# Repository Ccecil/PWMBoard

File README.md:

This board is to be used to expand the PWM header from a V2 Smoothieboard (or Gadgeteer) header.  

- 4 mosfet buffered PWM outputs with jumper options to select between Pullup voltages and/or disable the pullup resistor for Opendrain outputs.
- 2 Switch inputs which are debounced with passives and have optional pullup resistor/voltage.
- 1 Comparator probe input which increases the repeatability of probes and allows use of probe voltages from 3-45v (through jumper configs)
- Optional voltage input for using higher voltages on the PWM output pin3 (i.e. Running higher voltages to the servo motor or using different 5v source)

Comparator probe input jumper options

- J5 pin 3 input voltage set to
- 2.9v-5v (default)
- 5-24v (JP5-2 cut)
- 6-45v (JP5-2 and JP5-3 cut)

PWM output and Switch input jumpers.

- JP2: J6-J9 pin 3 optional voltage source select (J1 Pin 2 default, cut to use J2 Pin 1)
- JP3-1: J3 pin 1 and pin 3 pullup Voltage select
- JP3-2: J3 pin 3 pullup disable
- JP4-1: J4 pin 1 and pin 3 pullup Voltage select
- JP4-2: J4 pin 3 pullup disable
- JP5-1: J5 pin 1 Voltage select
- JP5-2: J5 pin 3 pullup cut (required for HV operation)
- JP5-3: J5 pin 3 Low/High voltage select (default low)
- JP6: J6 pin 1 pullup Voltage select
- JP7: J7 pin 1 pullup Voltage select
- JP8: J8 pin 1 pullup Voltage select
- JP9: J9 pin 1 pullup Voltage select

Jumper and connector numbers match their respective driving pin from the J1 header

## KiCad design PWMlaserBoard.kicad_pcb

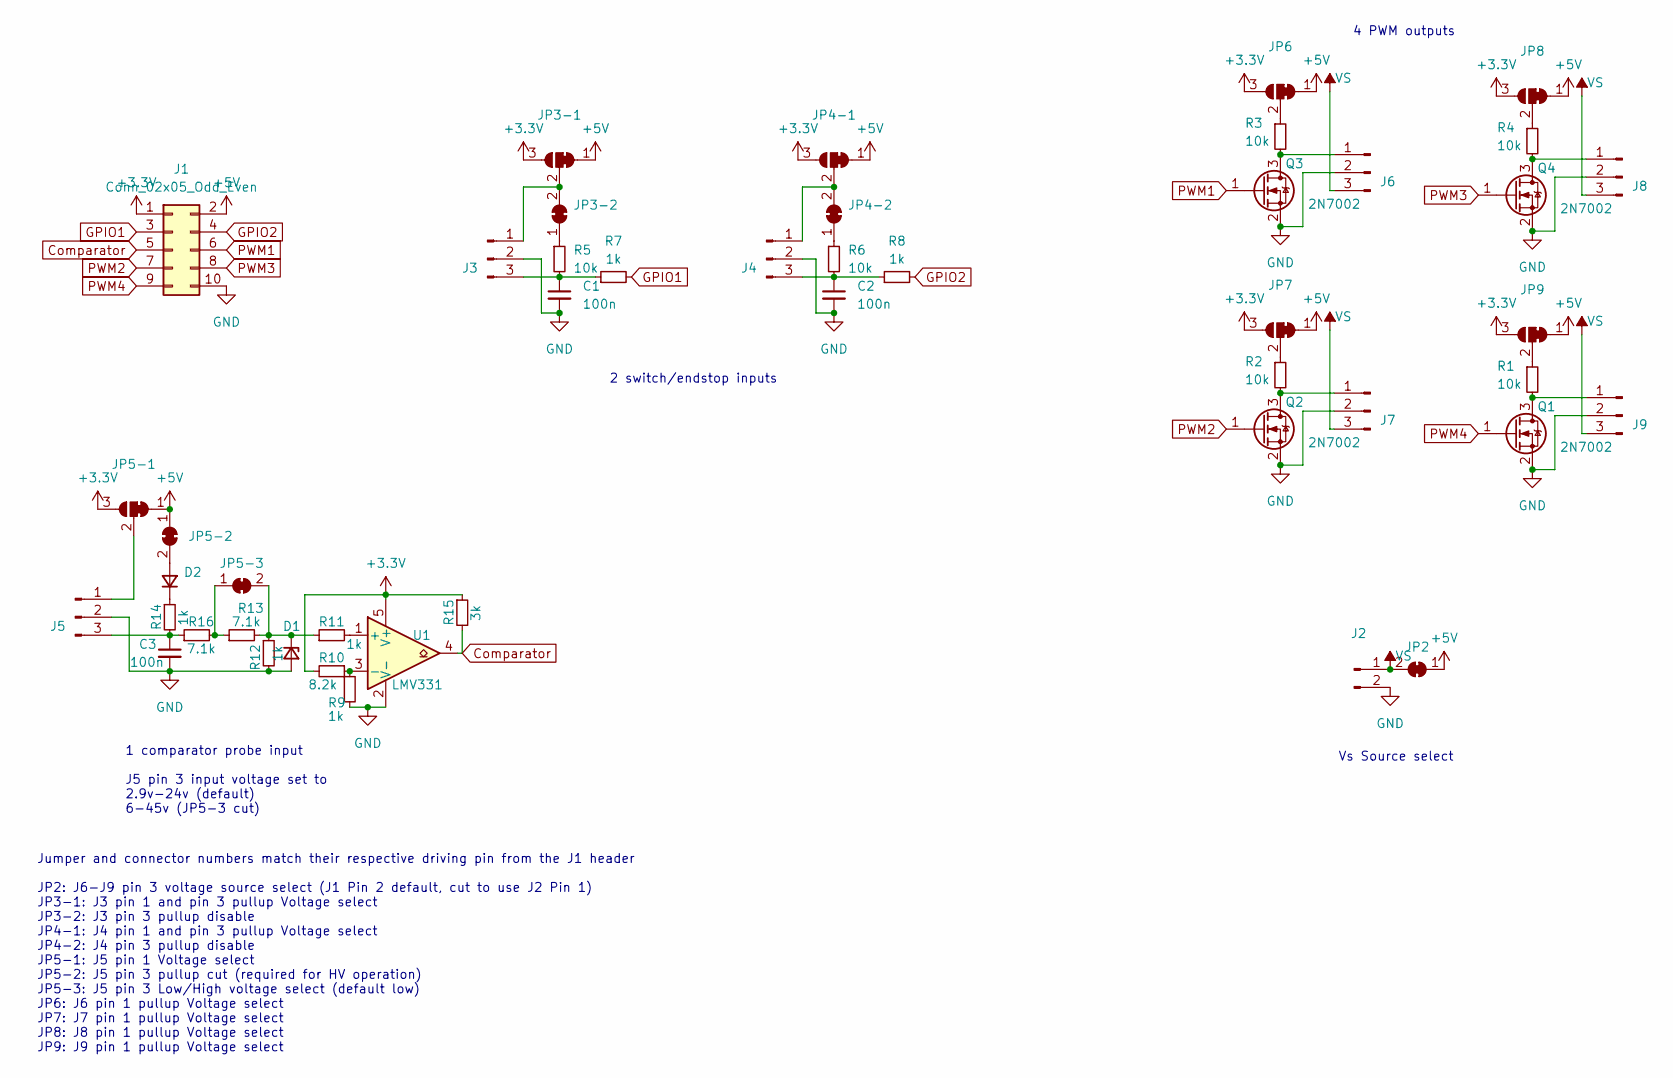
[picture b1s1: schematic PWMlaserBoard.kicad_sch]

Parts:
C1, C2, C3: 100n; C_0402_1005Metric
D1: D_Zener_Small; D_0402_1005Metric
D2: D_Small; D_SOD-323
J1: Conn_02x05_Odd_Even; PinHeader_2x05_P1.27mm_Vertical_SMD
J2: Conn_01x02_Pin; Molex_KK-254_AE-6410-02A_1x02_P2.54mm_Vertical
J3, J4, J5, J6, J7, J8, J9: Conn_01x03_Pin; Molex_KK-254_AE-6410-03A_1x03_P2.54mm_Vertical
JP2, JP3-2, JP4-2, JP5-2, JP5-3: SolderJumper_2_Bridged; SolderJumper-2_P1.3mm_Bridged_RoundedPad1.0x1.5mm
JP3-1, JP4-1, JP5-1, JP6, JP7, JP8, JP9: SolderJumper_3_Bridged12; SolderJumper-3_P1.3mm_Bridged12_RoundedPad1.0x1.5mm
Q1, Q2, Q3, Q4: 2N7002; SOT-23
R1, R2, R3, R4, R5, R6: 10k; R_0402_1005Metric
R7, R8, R9, R11, R12, R14: 1k; R_0402_1005Metric
R10: 8.2k; R_0402_1005Metric
R13, R16: 7.1k; R_0402_1005Metric
R15: 3k; R_0402_1005Metric
U1: LMV331; SOT-23-5

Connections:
+3.3V: J1.1, JP3-1.3 (B), JP4-1.3 (B), JP5-1.3 (B), JP6.3 (B), JP7.3 (B), JP8.3 (B), JP9.3 (B), R10.2, R15.1, U1.5 (V+)
+5V: J1.2, JP2.1 (A), JP3-1.1 (A), JP4-1.1 (A), JP5-1.1 (A), JP5-2.1 (A), JP6.1 (A), JP7.1 (A), JP8.1 (A), JP9.1 (A)
Comparator: J1.5, R15.2, U1.4
GND: C1.2, C2.2, C3.2, D1.2 (A), J1.10, J2.2, J3.2, J4.2, J5.2, J6.2, J7.2, J8.2, J9.2, Q1.2 (S), Q2.2 (S), Q3.2 (S), Q4.2 (S), R9.2, R12.2, U1.2 (V-)
GPIO1: J1.3, R7.2
GPIO2: J1.4, R8.2
unnamed: D1.1 (K), JP5-3.2 (B), R11.1, R12.1, R13.2
unnamed: D2.2 (A), JP5-2.2 (B)
unnamed: D2.1 (K), R14.1
unnamed: J3.1, JP3-1.2 (C), JP3-2.2 (B)
unnamed: C1.1, J3.3, R5.2, R7.1
unnamed: J4.1, JP4-1.2 (C), JP4-2.2 (B)
unnamed: C2.1, J4.3, R6.2, R8.1
unnamed: J5.1, JP5-1.2 (C)
unnamed: C3.1, J5.3, R14.2, R16.1
unnamed: J6.1, Q3.3 (D), R3.2
unnamed: J7.1, Q2.3 (D), R2.2
unnamed: J8.1, Q4.3 (D), R4.2
unnamed: J9.1, Q1.3 (D), R1.2
unnamed: JP3-2.1 (A), R5.1
unnamed: JP4-2.1 (A), R6.1
unnamed: JP5-3.1 (A), R13.1, R16.2
unnamed: JP6.2 (C), R3.1
unnamed: JP7.2 (C), R2.1
unnamed: JP8.2 (C), R4.1
unnamed: JP9.2 (C), R1.1
unnamed: R11.2, U1.1 (+)
unnamed: R9.1, R10.1, U1.3 (-)
PWM1: J1.6, Q3.1 (G)
PWM2: J1.7, Q2.1 (G)
PWM3: J1.8, Q4.1 (G)
PWM4: J1.9, Q1.1 (G)
VS: J2.1, J6.3, J7.3, J8.3, J9.3, JP2.2 (B)

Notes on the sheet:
4 PWM outputs
Vs Source select
2 switch/endstop inputs
Jumper and connector numbers match their respective driving pin from the J1 header JP2: J6-J9 pin 3 voltage source select (J1 Pin 2 default, cut to use J2 Pin 1) JP3-1: J3 pin 1 and pin 3 pullup Voltage select JP3-2: J3 pin 3 pullup disable JP4-1: J4 pin 1 and pin 3 pullup Voltage select JP4-2: J4 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
1 comparator probe input J5 pin 3 input voltage set to 2.9v-24v (default) 6-45v (JP5-3 cut)

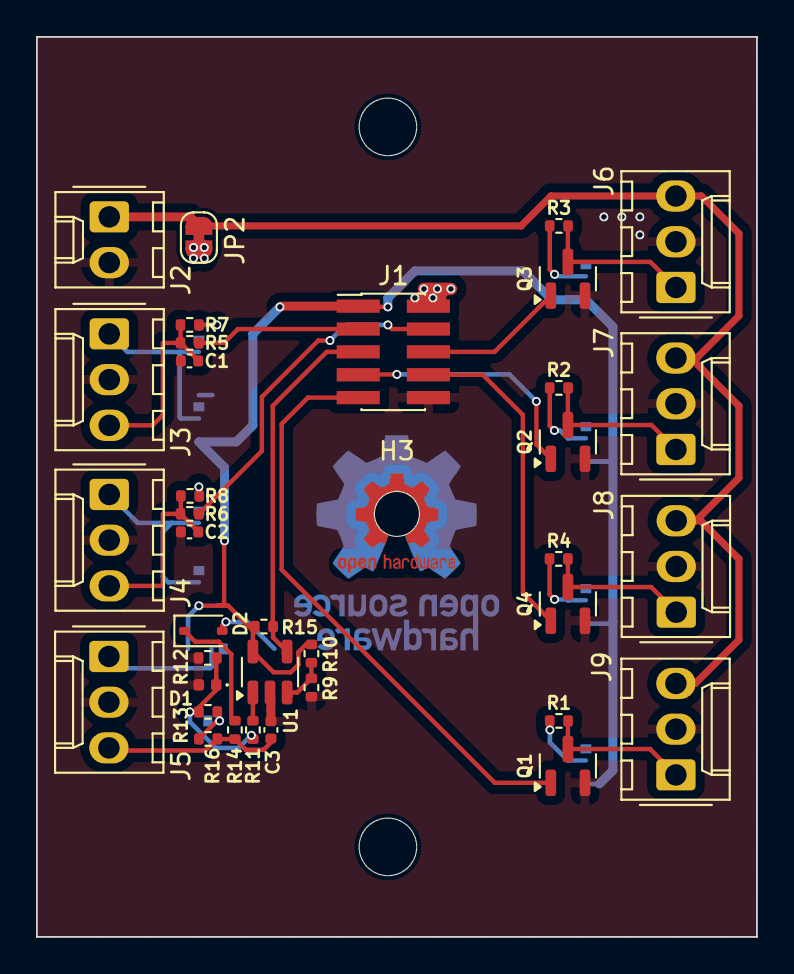
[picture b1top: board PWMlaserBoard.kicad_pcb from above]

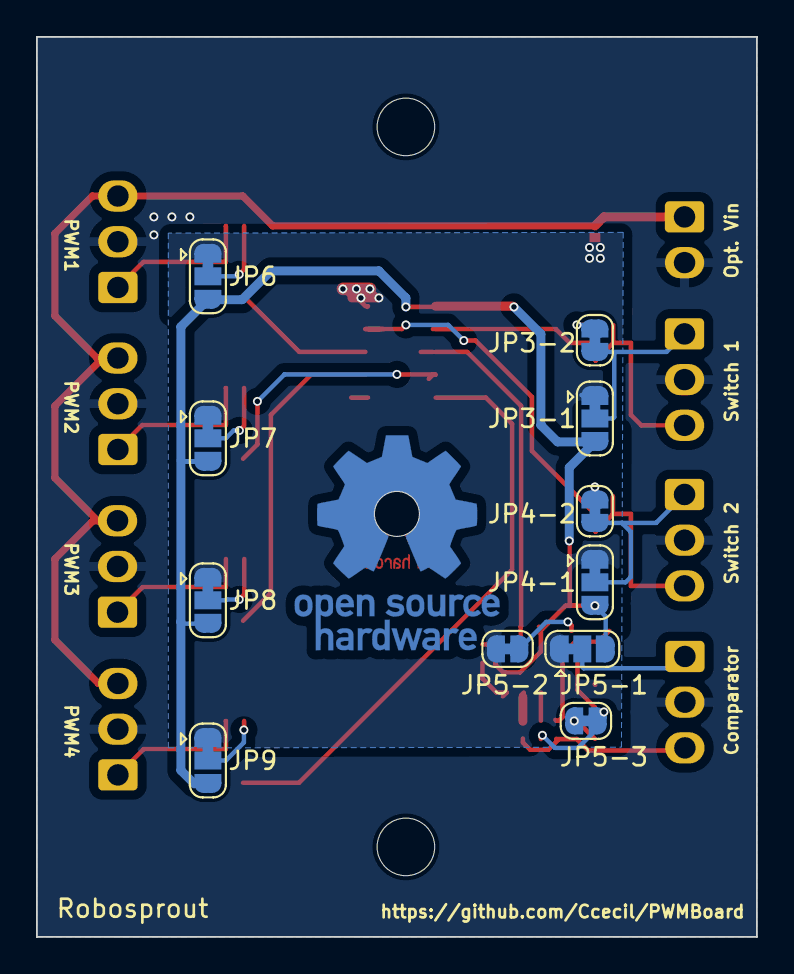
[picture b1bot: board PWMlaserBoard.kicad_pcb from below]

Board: 2 copper layers, 40.0 x 50.0 mm, 50 parts (11 on the bottom side), 33 nets.

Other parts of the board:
H1, H2: MountingHole; MountingHole_3.2mm_M3
H3: StencilHole; MountingHole_2.5mm

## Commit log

2024-05-05 Initial upload
    Finished but untested.
2024-05-05 Create README.md
    First readme
    Basic description
2024-05-05 Update README.md
    fix format
